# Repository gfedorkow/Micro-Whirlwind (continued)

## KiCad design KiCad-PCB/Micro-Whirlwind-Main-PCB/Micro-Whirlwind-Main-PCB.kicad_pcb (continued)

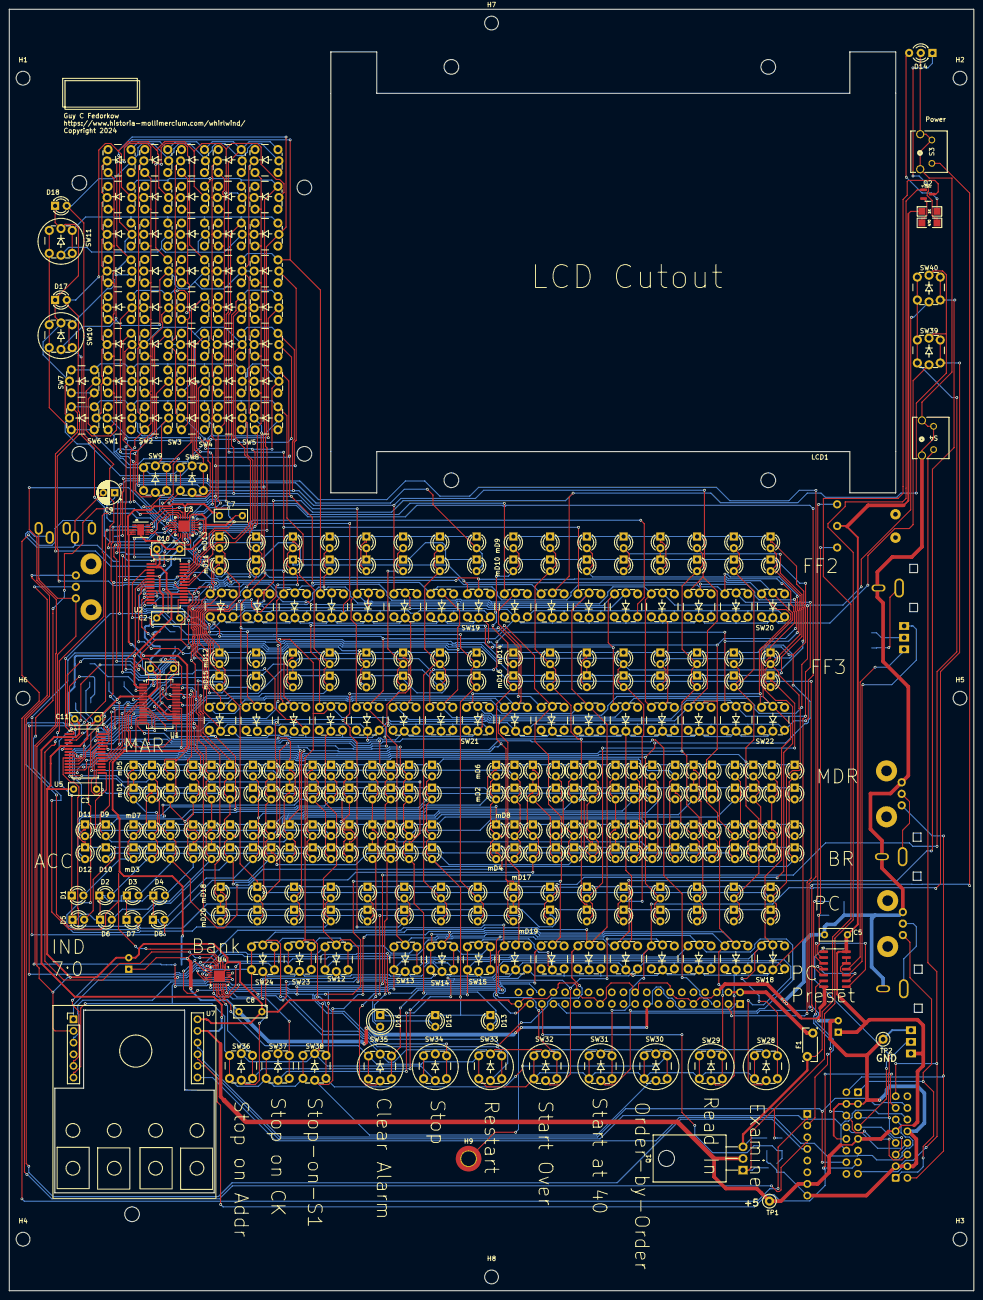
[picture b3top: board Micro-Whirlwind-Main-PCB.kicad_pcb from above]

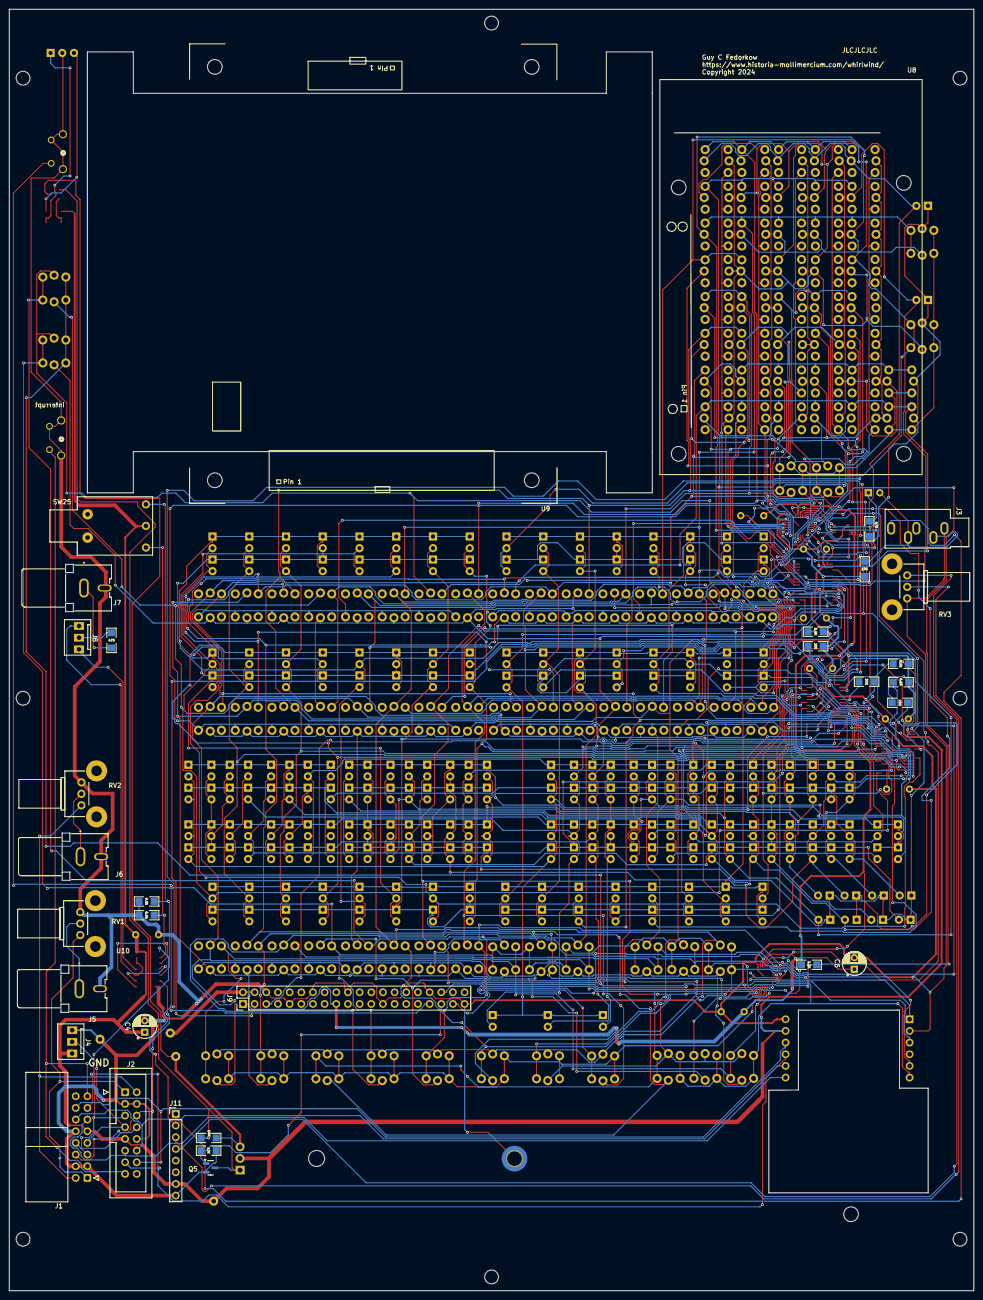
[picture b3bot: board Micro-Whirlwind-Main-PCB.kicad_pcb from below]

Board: 2 copper layers, 209.9 x 278.9 mm, 143 parts (21 on the bottom side), 139 nets.

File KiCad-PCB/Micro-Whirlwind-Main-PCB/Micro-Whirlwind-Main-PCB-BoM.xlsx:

Reference | Value | Datasheet | Footprint | Qty | DNP
C1,C2,C3,C5,C7,C8,C10,C11 | 0.1uF | ~ | Capacitor_THT:C_Rect_L7.0mm_W2.5mm_P5.00mm | 8
C4,C6 | 47uf | ~ | Capacitor_THT:CP_Radial_D5.0mm_P2.50mm | 2
C9 | 22uf | ~ | Capacitor_THT:CP_Radial_D5.0mm_P2.50mm | 1
D1,D2,D3,D4,D5,D6,D7,D8,D9,D10,D11,D12,D13,D15,D16,D17,D18 | LED | ~ | -- mixed values -- | 17
D14 | LED_Dual_AKA | ~ | LED_THT:LED_D3.0mm-3 | 1
F1 | Polyfuse | ~ | Fuse:Fuse_Bourns_MF-RG300 | 1
J1,J2 | Conn_02x08_Odd_Even | ~ | -- mixed values -- | 2
J3 | AudioJack3_Ground_SwitchTR | ~ | Connector_Audio:Jack_3.5mm_CUI_SJ1-3535NG_Horizontal | 1
J4,J8 | Conn_01x03 | ~ | mWW-Project-Library:PSS_3 | 2
J5 | X | ~ | mWW-Project-Library:CUI_RCJ-041 | 1
J6 | Y | ~ | mWW-Project-Library:CUI_RCJ-041 | 1
J7 | Z | ~ | mWW-Project-Library:CUI_RCJ-041 | 1
J9 | RaspiGPIO40 |  | Connector_PinHeader_2.54mm:PinHeader_2x20_P2.54mm_Vertical | 1
J11 | Conn_01x08 | ~ | Connector_PinHeader_2.54mm:PinHeader_1x08_P2.54mm_Vertical | 1
L1,LCD1,mD1,mD2,mD3,mD4,mD5,mD6,mD7,mD8,mD9,mD10,mD11,mD12,mD13,mD14,mD15,mD16,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 | ~ |  | -- mixed values -- | 23
Q1 | IRF5305 | http://www.irf.com/product-info/datasheets/data/irf9540n.pdf | Package_TO_SOT_THT:TO-220-3_Horizontal_TabDown | 1
Q2,Q5 | BSS138 | https://www.onsemi.com/pub/Collateral/BSS138-D.PDF | Package_TO_SOT_SMD:SOT-23 | 2
R1,R9,R10 | 6.8k | ~ | mWW-Project-Library:SM-1206B | 3
R2,R4,R6 | 20K | ~ | mWW-Project-Library:SM-1206B | 3
R3,R5 | 6.8K | ~ | mWW-Project-Library:SM-1206B | 2
R7,R11,R18 | 470 | ~ | mWW-Project-Library:SM-1206B | 3
R8 | 2.2K | ~ | mWW-Project-Library:SM-1206B | 1
R12,R15,R16 | 10K | ~ | mWW-Project-Library:SM-1206B | 3
R17 | 1K | ~ | mWW-Project-Library:SM-1206B | 1
RV1,RV2,RV3 | 10k | ~ | Potentiometer_THT:Potentiometer_Bourns_PTV09A-2_Single_Horizontal | 3
S3,S4 | RA_Push | -- mixed values -- | mWW-Project-Library:SW_KSA0V311LFTR_CNK-RA-pushbutton | 2
SW1,SW2,SW3,SW4,SW5,SW18,SW19,SW20,SW21,SW22 | mSW_Push_LEDx8 | ~ | mWW-Project-Library:mILS-TB-140-SW_PUSH_and_LED_6mm_x8 | 10
SW6,SW7,SW8,SW9,SW10,SW11,SW12,SW13,SW14,SW15,SW23,SW24,SW28,SW29,SW30,SW31,SW3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 | SW_Push_LED | ~ | -- mixed values -- | 25
SW25 | SW_SPDT_MSM | https://www.apem.com/idec-apem/en_US/medias/toggle-switches-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 | mWW-Project-Library:SPDT-Toggle-Right-Angle | 1
TP1,TP2 | TestPoint | ~ | TestPoint:TestPoint_Loop_D2.50mm_Drill1.0mm | 2
U1,U2,U5 | IS31FL3731-SA | http://www.issi.com/WW/pdf/31FL3731.pdf | Package_SO:SSOP-28_5.3x10.2mm_P0.65mm | 3
U3,U4 | TCA8418RTWR |  | mWW-Project-Library:QFN50P400X400X80-25N | 2
U6 | LTC4316IDD_PBF |  | mWW-Project-Library:DFN-10_DD-with-clearance | 1
U8 | RasPi Outline |  | mWW-Project-Library:RasPi-Outline | 1
U9 | D_to_A_Outline |  | mWW-Project-Library:D_to_A_Outline | 1
U10 | 4001 | http://www.intersil.com/content/dam/Intersil/documents/cd40/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 | Package_SO:SOIC-14_3.9x8.7mm_P1.27mm | 1

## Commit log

2024-11-28 adding more initial files
2024-11-28 test-push
2024-11-28 removing duplicates
2024-11-28 print one more key param
2024-11-29 tweaks to support rotary encoder
2025-02-12 backing out low-level bit reverse
2025-02-15 older version prior to adding function mapping
2025-02-22 fixing bugs in diag
2025-02-22 file name change
2025-02-22 file name changes
2025-02-23 adding a few more files plus register assignments
2025-02-23 started adding in ww register api
2025-02-28 starting to add cpu-to-LED mapping
2025-02-28 first round of typos
2025-02-28 starting experiment to emulate smbus on PC
2025-03-02 added more cpu registers to the Map test
2025-03-02 starting to add blue Preset LEDs
2025-03-03 started adding preset LEDs
2025-03-12 changes to blink blue lights; modify to test on the PC
2025-03-13 typos in chip drivers
2025-03-16 started mapping routine for mWW switch array
2025-03-16 fixed a bunch of typos
2025-03-16 started on button decoder
2025-03-17 fixed one typo to complete test
2025-03-17 linking FF preset switches and LEDs
2025-03-17 debug flip-flop preset register setting
2025-03-18 connecting switches to MIR leds
2025-03-19 more debug of MIR
2025-03-22 starting to stitch the mWW material on to the native simulator classes
2025-03-22 added pc-preset code; fixed a bug in LMIR/RMIR switches
2025-03-22 pushing debug changes from RasPi testing
2025-04-09 updates to register assignment drawing
2025-10-29 re-initializing Micro-Whirlwind repository
2025-10-29 fixed a broken symbolic link
2025-10-31 Add README with project description
2025-12-25 Fix typo in README description
2025-12-25 revised and tweaked Notes on PCB Corrections
2025-12-25 trying to figure out some weird cygwin permission problem...
2025-12-31 I made most of the corrections to the schematic and some to the PCB. The Main PCB needs to be redone with a four-layer PCB, so I didn't re-route all the traces on the PCB The Power switch needs to be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
2026-03-06 routine update of Notes files
2026-06-15 added one new LED to indicate that the Light Gun is active. See page 'Execution Control'
2026-06-27 added notes for hnf corrections
